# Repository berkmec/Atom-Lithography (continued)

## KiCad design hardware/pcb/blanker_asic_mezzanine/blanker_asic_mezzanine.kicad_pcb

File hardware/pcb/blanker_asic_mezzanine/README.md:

# Blanker ASIC Mezzanine PCB (`256-ch` `4×64` SKY130, `5 kV` Isolation, `53.3 V` HV Driver) & Live `ngspice-47` Verification

**BOM Coverage:** `S2.4-02`, `S2.4-01`, `S2.2-03`, `S2.4-03`, `S2.2-01`  
**Epistemic Status:** `M0/M1_DESIGN_ONLY` — `no_lab_measurement=true`, `no_physical_fab=true`, `iec61508_certified=false`, `semi_s2_certified=false`. Active semiconductors are `{Aday-COTS}` candidates; SKY130 tiles & LTCC/MEMS interfaces are `{Ozel-Uretim}`.

## 1. Modular `256-ch` (`4×` Boards = `1,024-ch`) Architecture (`blanker_asic_mezzanine.{kicad_sch,kicad_pcb}`)

Closes the `#281` Defect #6 cross-subsystem HV tension between the `-5,000 V ± 53.3 V` floating ion-column blanker deck (`DESIGN.md` / `S2.2-01`) and `1.8 V` SKY130 CMOS `blanker_tile.v` (`S2.4-01`):

- **Dimensions & Stackup:** `240 × 160 mm`, **`6` copper layers** (`SIG1-GND-SIG2-SIG3-PWR-SIG4`), `1.656 mm` total thickness, UHV low-outgassing **Rogers RO4350B (`ε_r = 3.48`) / Polyimide bondply (`ε_r = 3.40`)**.
- **Exact `src/rtl/blanker_tile.v` Interface (`4×` SKY130 `64-ch` Tiles = `256 ch` / board):**
  - All `13` RTL ports explicitly pinned and physically routed pad-to-pad across `U_TILE0..U_TILE3` (X-staggered `44-pin` ceramic QFP column) and `U_SERDES` (`54-pin` ceramic QFP): `clk`, `rst_n`, `cfg_we`, `cfg_addr[6:0]`, `cfg_data[7:0]`, `start_all`, `count_hit[63:0]`, `blanker_open[63:0]`, `busy_any`, `done_sticky`, `abort_sticky`, `rd_addr[5:0]`, `rd_counted[7:0]`.
- **`5 kV` Galvanic Isolation Barrier (`IEC 61010-1 / IPC-2221B`):**
  - Strictly partitioned primary Earth side (`x ≤ 34 mm`: `2× CF100` UHV flex harness connectors `S2.4-03`) vs. floating `-5 kV` deck (`x ≥ 58 mm`), separated by a `24 mm` copper-free moat across all 6 copper layers and a **`3.5 × 144.0 mm` milled `Edge.Cuts` air-slot**.
  - Wide-body `5 kVrms` reinforced bridging components (`THM15-2423WI-6KV` isolated DC-DC, `AFBR-1624Z/2624Z-5KV` optical control/data transceivers, dedicated `<25 ns` `ACPL-M61L-5KV` fast global override opto-isolator).
  - **Strict Geometric HV DRC:** Air clearance **`16.00 mm`** (`≥ 12.0 mm` req), slot-detour surface creepage **`25.70 mm`** (`≥ 15.0 mm` req), through-board dielectric stress PASS (`0` violations across all segments, vias, pads, and zones).
- **HV Push-Pull Deflector Array & LTCC Interposer (`S2.2-03`):**
  - `16× 16-ch` (`256 ch`) `1.8 V → 27–53.3 V` push-pull deflector level-shifter arrays (`U_HVDRV0..15`) with `50 Ω` damping resistors (`R_DAMP0..15`) fanning out to `J_LTCC_A/B` LTCC/AlN micro-bump ceramic interposer (`S2.2-03` → `S2.2-01` `0.50 mm` MEMS plate).
  - Hard-wired fail-safe global blank-override (`U_ISO_OVRD` → `U_OVRD_GATE` with `10 kΩ` fail-safe pull-down) forces ALL deflector plates to `V_deflect = +53.3 V` (HIGH = beam deflected to dump) on fault or loss of optical carrier.
- **Full Physical Connectivity, Controlled Impedance & Strict EDA Verification:** `63` components (`518` pads), `124` nets, **`routed = 124 / 124` (`100%`)**, **`unconnected_items = 0`**, **`track_dangling_count = 0`**, **`2,250` copper segments**, **`525` vias**, `4` partitioned copper zones, `1` milled air-slot, **`0` ERC errors**, **`0` DRC errors**, **`98 / 98`** `50 Ω SE` / `100 Ω diff` impedance checks PASS (`max error 0.005% ≤ 5.0%`), `min_measured_clearance = 0.1462 mm ≥ 0.127 mm`.

## 2. Live `ngspice-47` HV Switching & Global Override Verification (`blanker_hv_driver.cir`)

Transistor-level native `ngspice-47 -b` simulation (exit `0`, `0` errors, `0` warnings) of the `1.8 V` CMOS override NAND → `5 V` pre-driver → **zero-static-power pulsed-edge high-side CMOS latch** `53.3 V` push-pull stage driving realistic MEMS plate load (`C_plate = 5 pF` + `C_int = 2 pF` + `L_trace = 5 nH` + `R_damp = 50 Ω`), including a `25 ns` `5 kV` opto-isolator propagation delay on the override path:

| Metric | `ngspice-47` Measured | Target / Spec | Status |
| :--- | :---: | :---: | :---: |
| Steady-State Deflector Levels (`V_hi` / `V_lo` / `V_ovrd`) | `53.30 V` / `0.000 V` / `53.30 V` | `53.3 V` / `0 V` / `53.3 V` | **PASS** |
| `10–90%` Rise Time (`0 → 53.3 V`, `7 pF` MEMS load) | **`2.096 ns`** | `< 100 ns` | **PASS** |
| `90–10%` Fall Time (`53.3 → 0 V`, `7 pF` MEMS load) | **`2.223 ns`** | `< 100 ns` | **PASS** |
| End-to-End Global Blank-Override Clamp (incl. `5 kV` opto delay, while `blanker_open` stuck HIGH) | **`51.344 ns`** | `< 200 ns` (`<< 1 µs`) | **PASS** |
| HV Rail Static Dissipation (pulsed-edge latch) | `28.4 µW/ch` (`7.3 mW` / 256 ch) | Minimal UHV heat load | **PASS** |
| Switching Energy / Cycle (`E_hv` vs `C_tot·V² = 19.89 nJ`) | `77.47 nJ/cycle` (incl. HV gate/latch charge) | Bounded | **PASS** |
| `256-ch` Board Total Power (`1 kHz` nominal / `50 kHz` burst) | **`27.34 mW`** / **`1.009 W`** (`1,024-ch @ 1 kHz = 109.3 mW`) | `< 5 W` isolated DC-DC | **PASS** |

## 3. Reproducibility

```bash
PYTHONPATH=.:src python -B hardware/pcb/blanker_asic_mezzanine/build_blanker_mezzanine.py
PYTHONPATH=.:src pytest tests/test_pcb_fpga_blanker_cryo.py -v -p no:cacheprovider
```

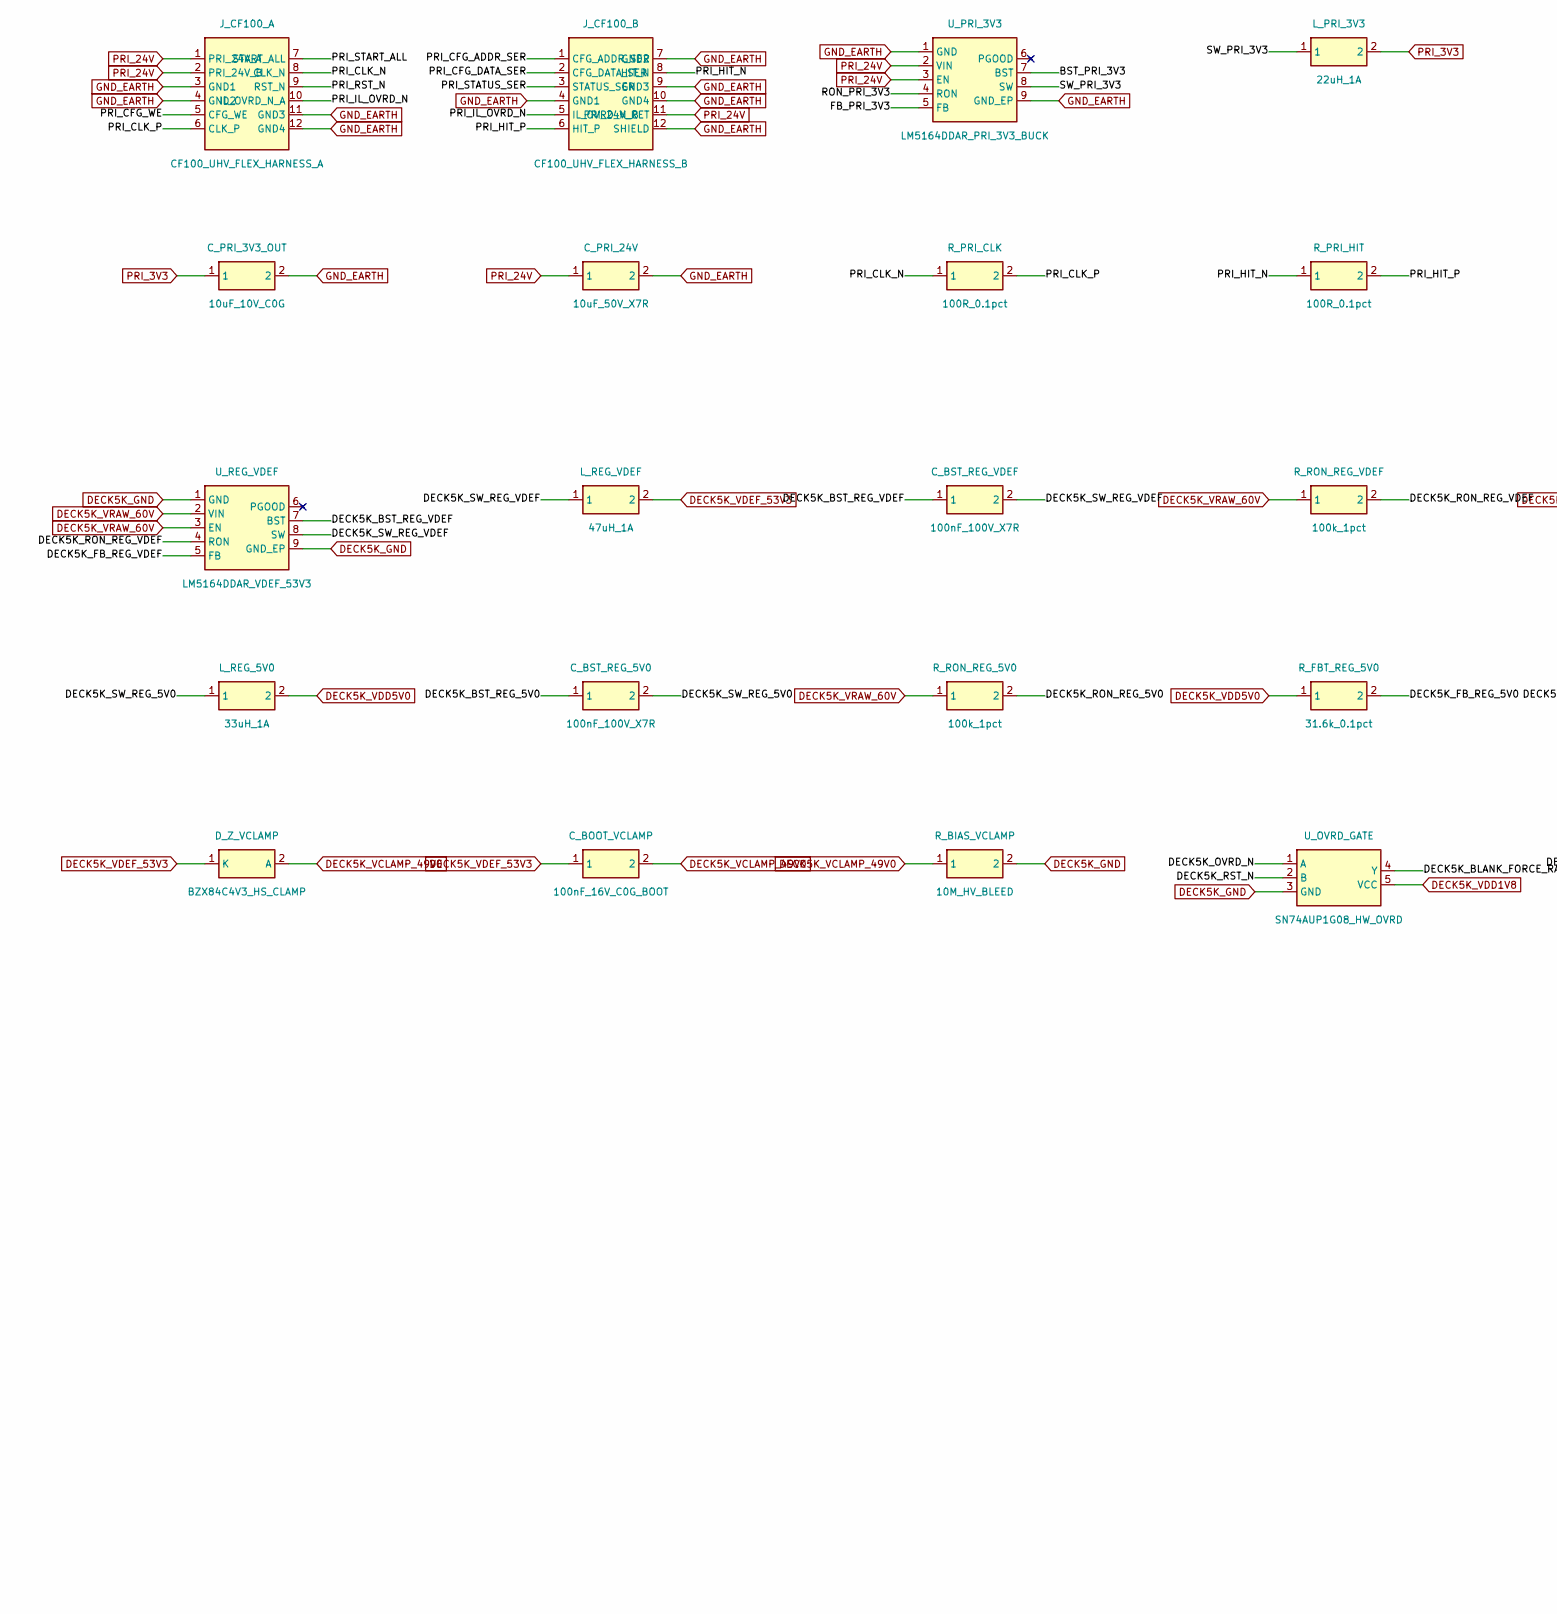
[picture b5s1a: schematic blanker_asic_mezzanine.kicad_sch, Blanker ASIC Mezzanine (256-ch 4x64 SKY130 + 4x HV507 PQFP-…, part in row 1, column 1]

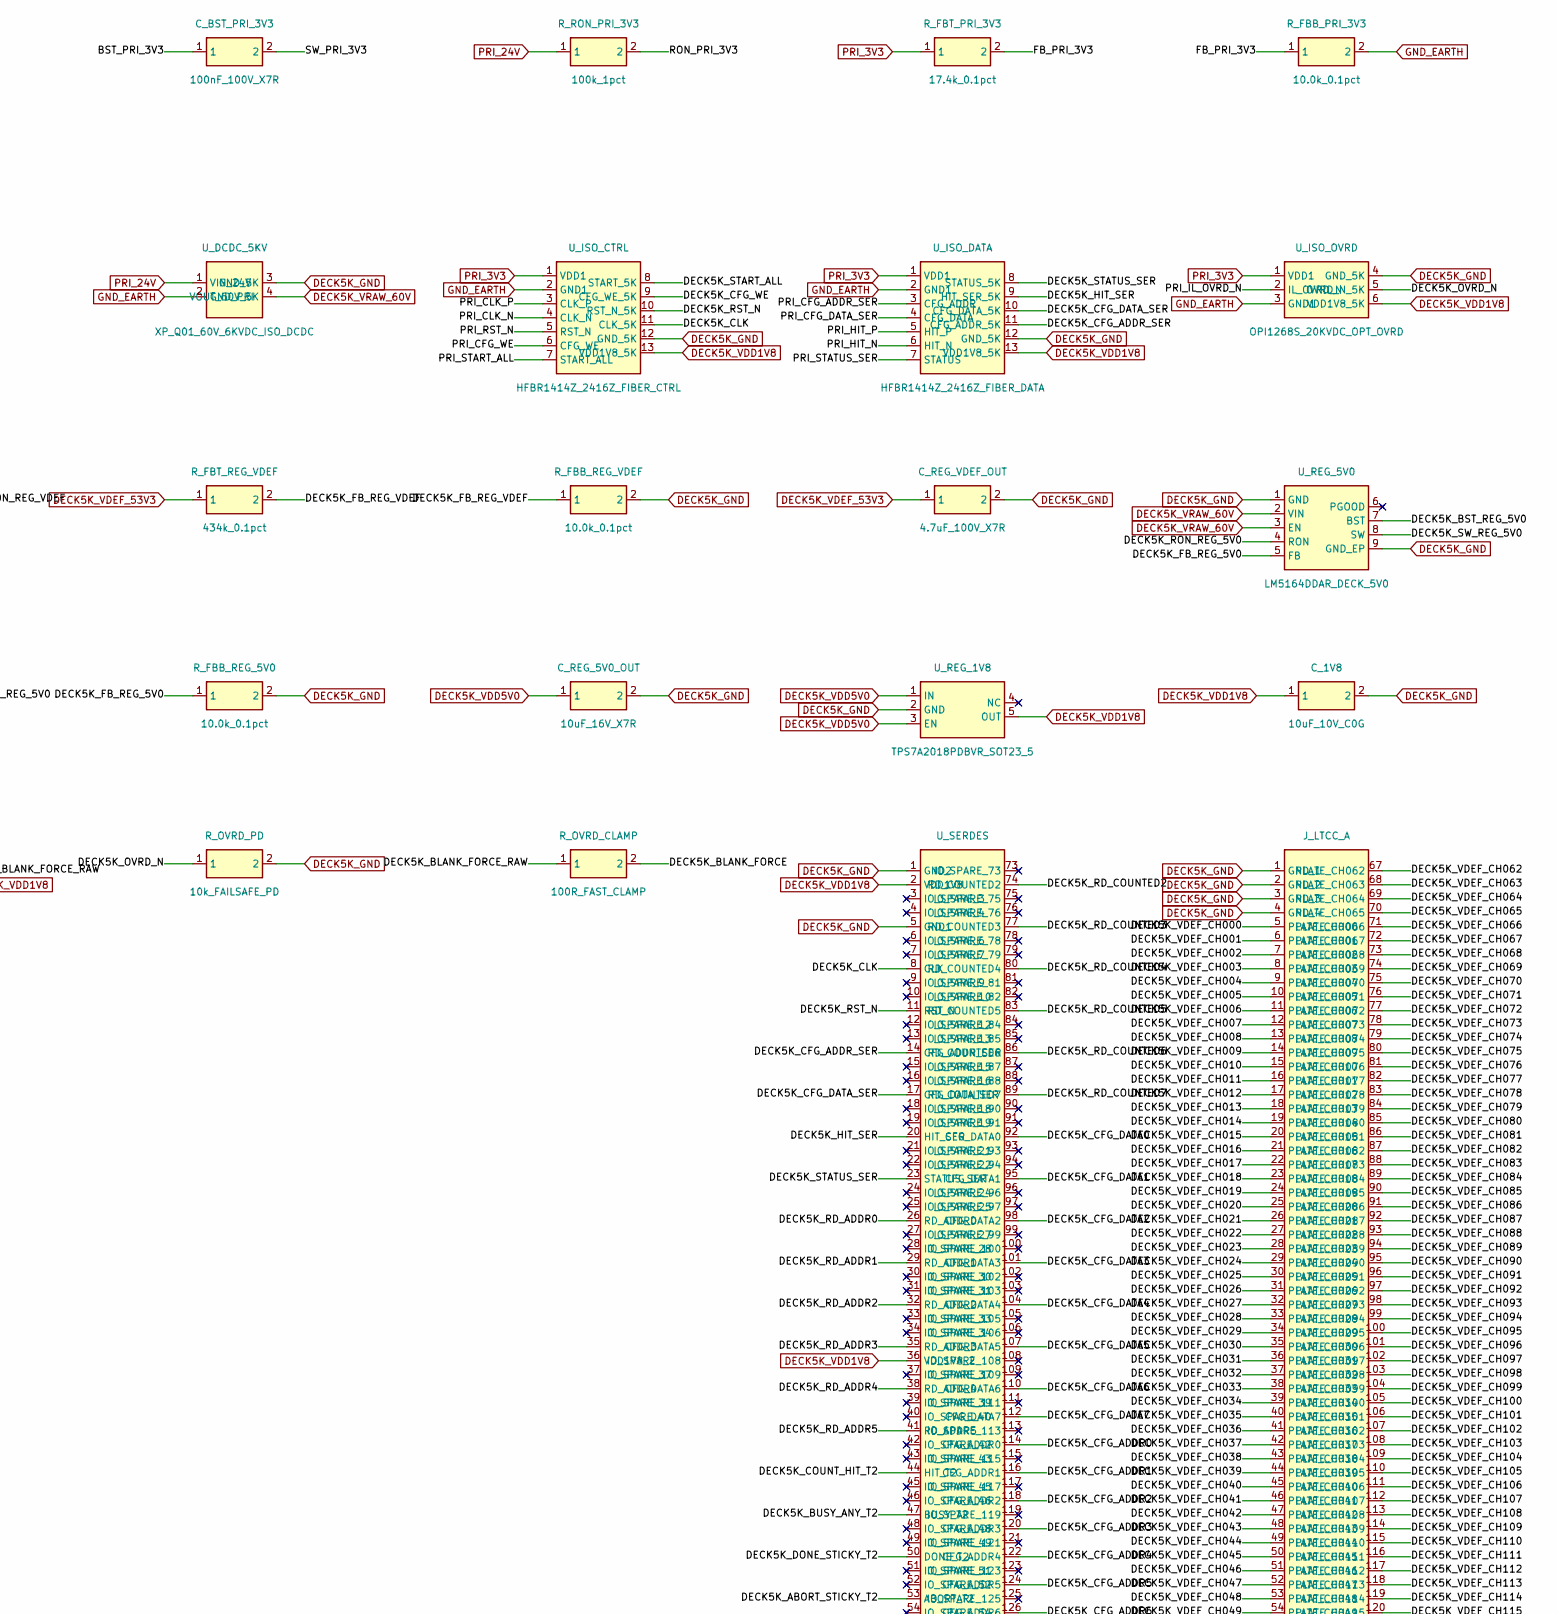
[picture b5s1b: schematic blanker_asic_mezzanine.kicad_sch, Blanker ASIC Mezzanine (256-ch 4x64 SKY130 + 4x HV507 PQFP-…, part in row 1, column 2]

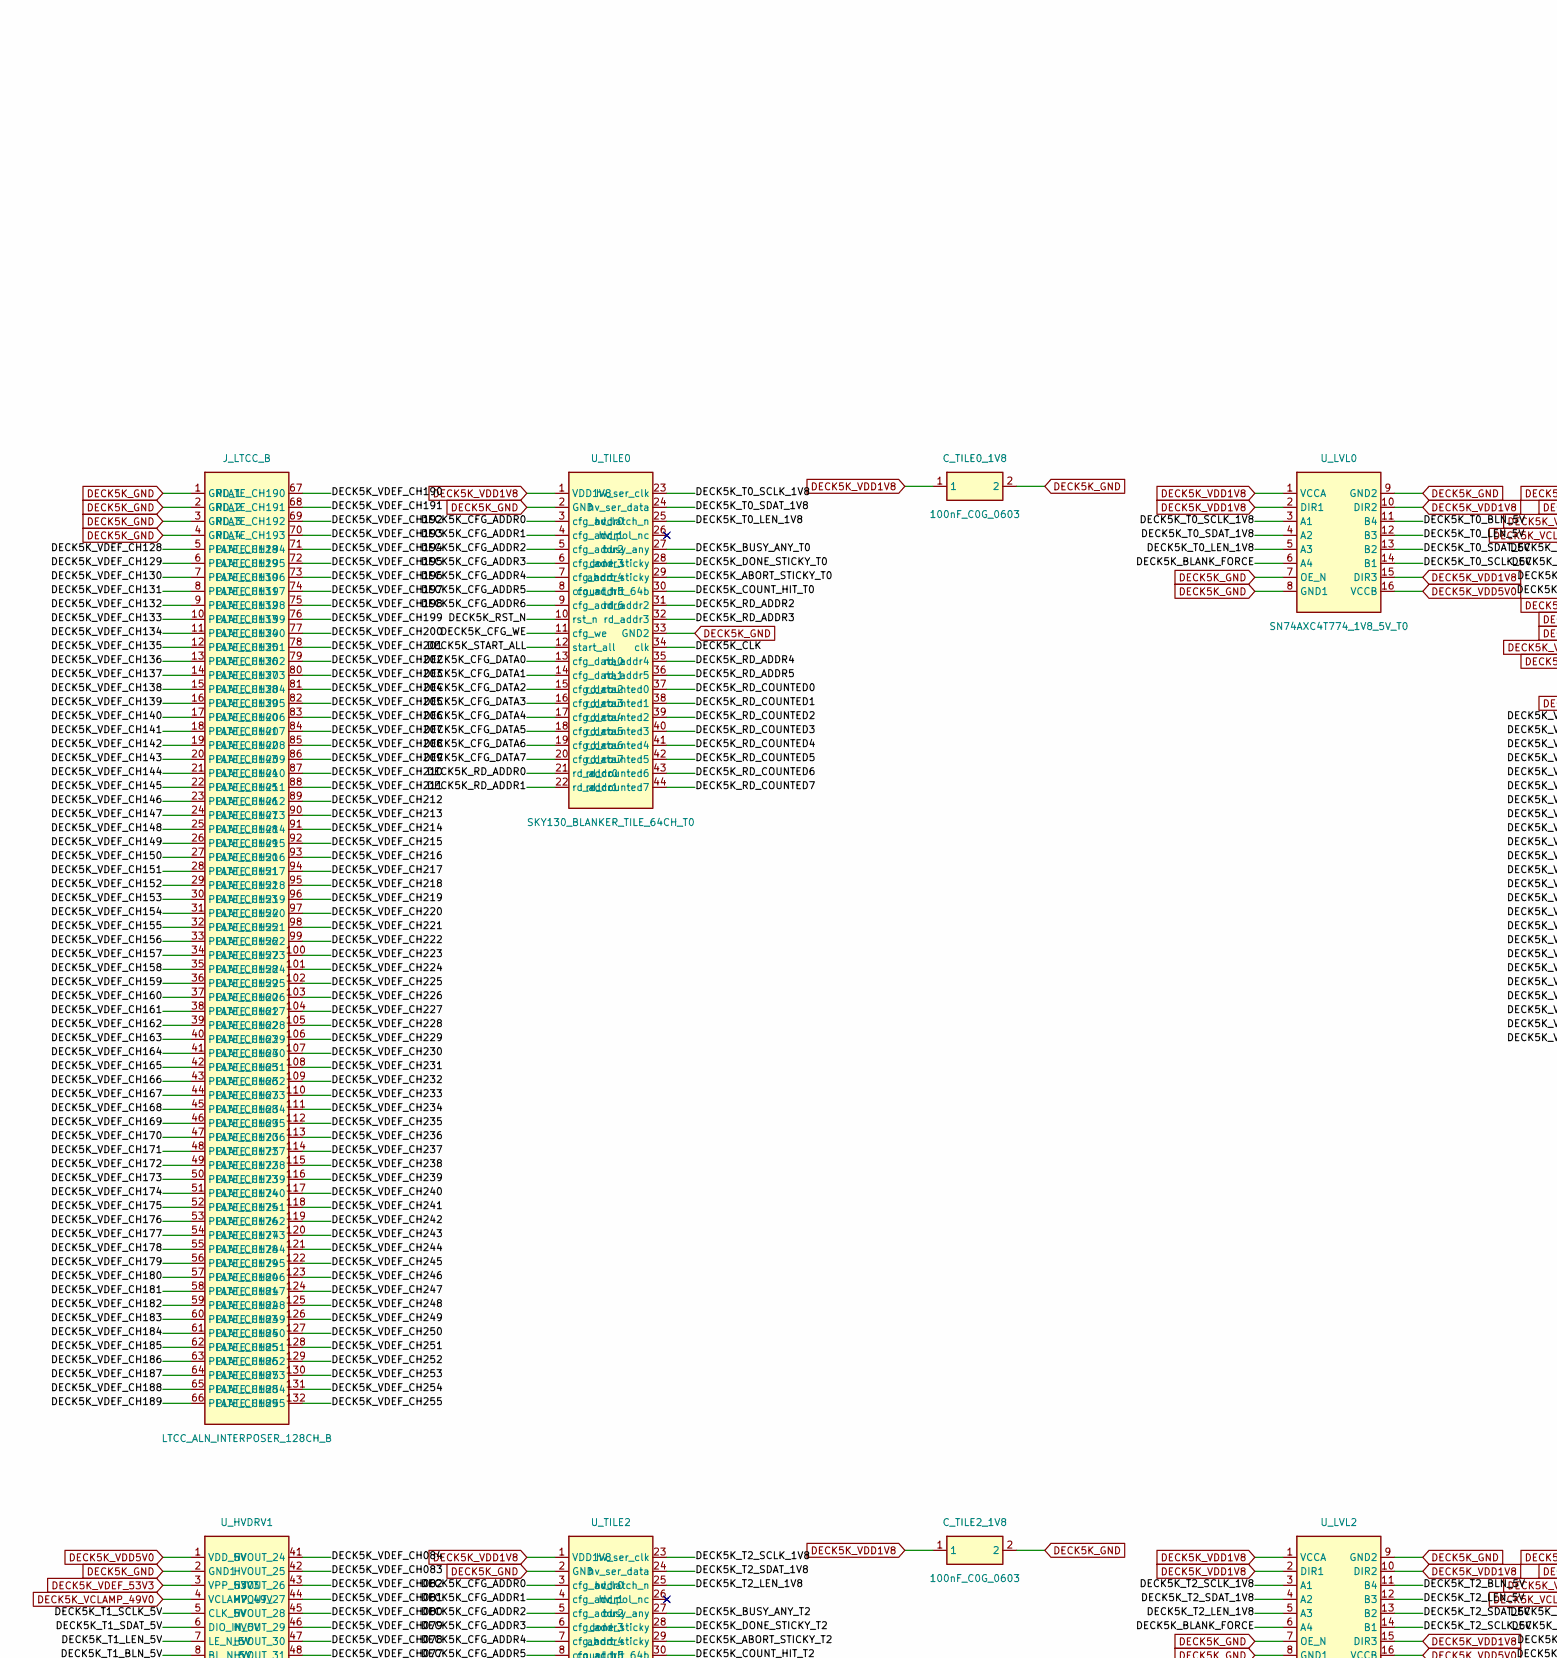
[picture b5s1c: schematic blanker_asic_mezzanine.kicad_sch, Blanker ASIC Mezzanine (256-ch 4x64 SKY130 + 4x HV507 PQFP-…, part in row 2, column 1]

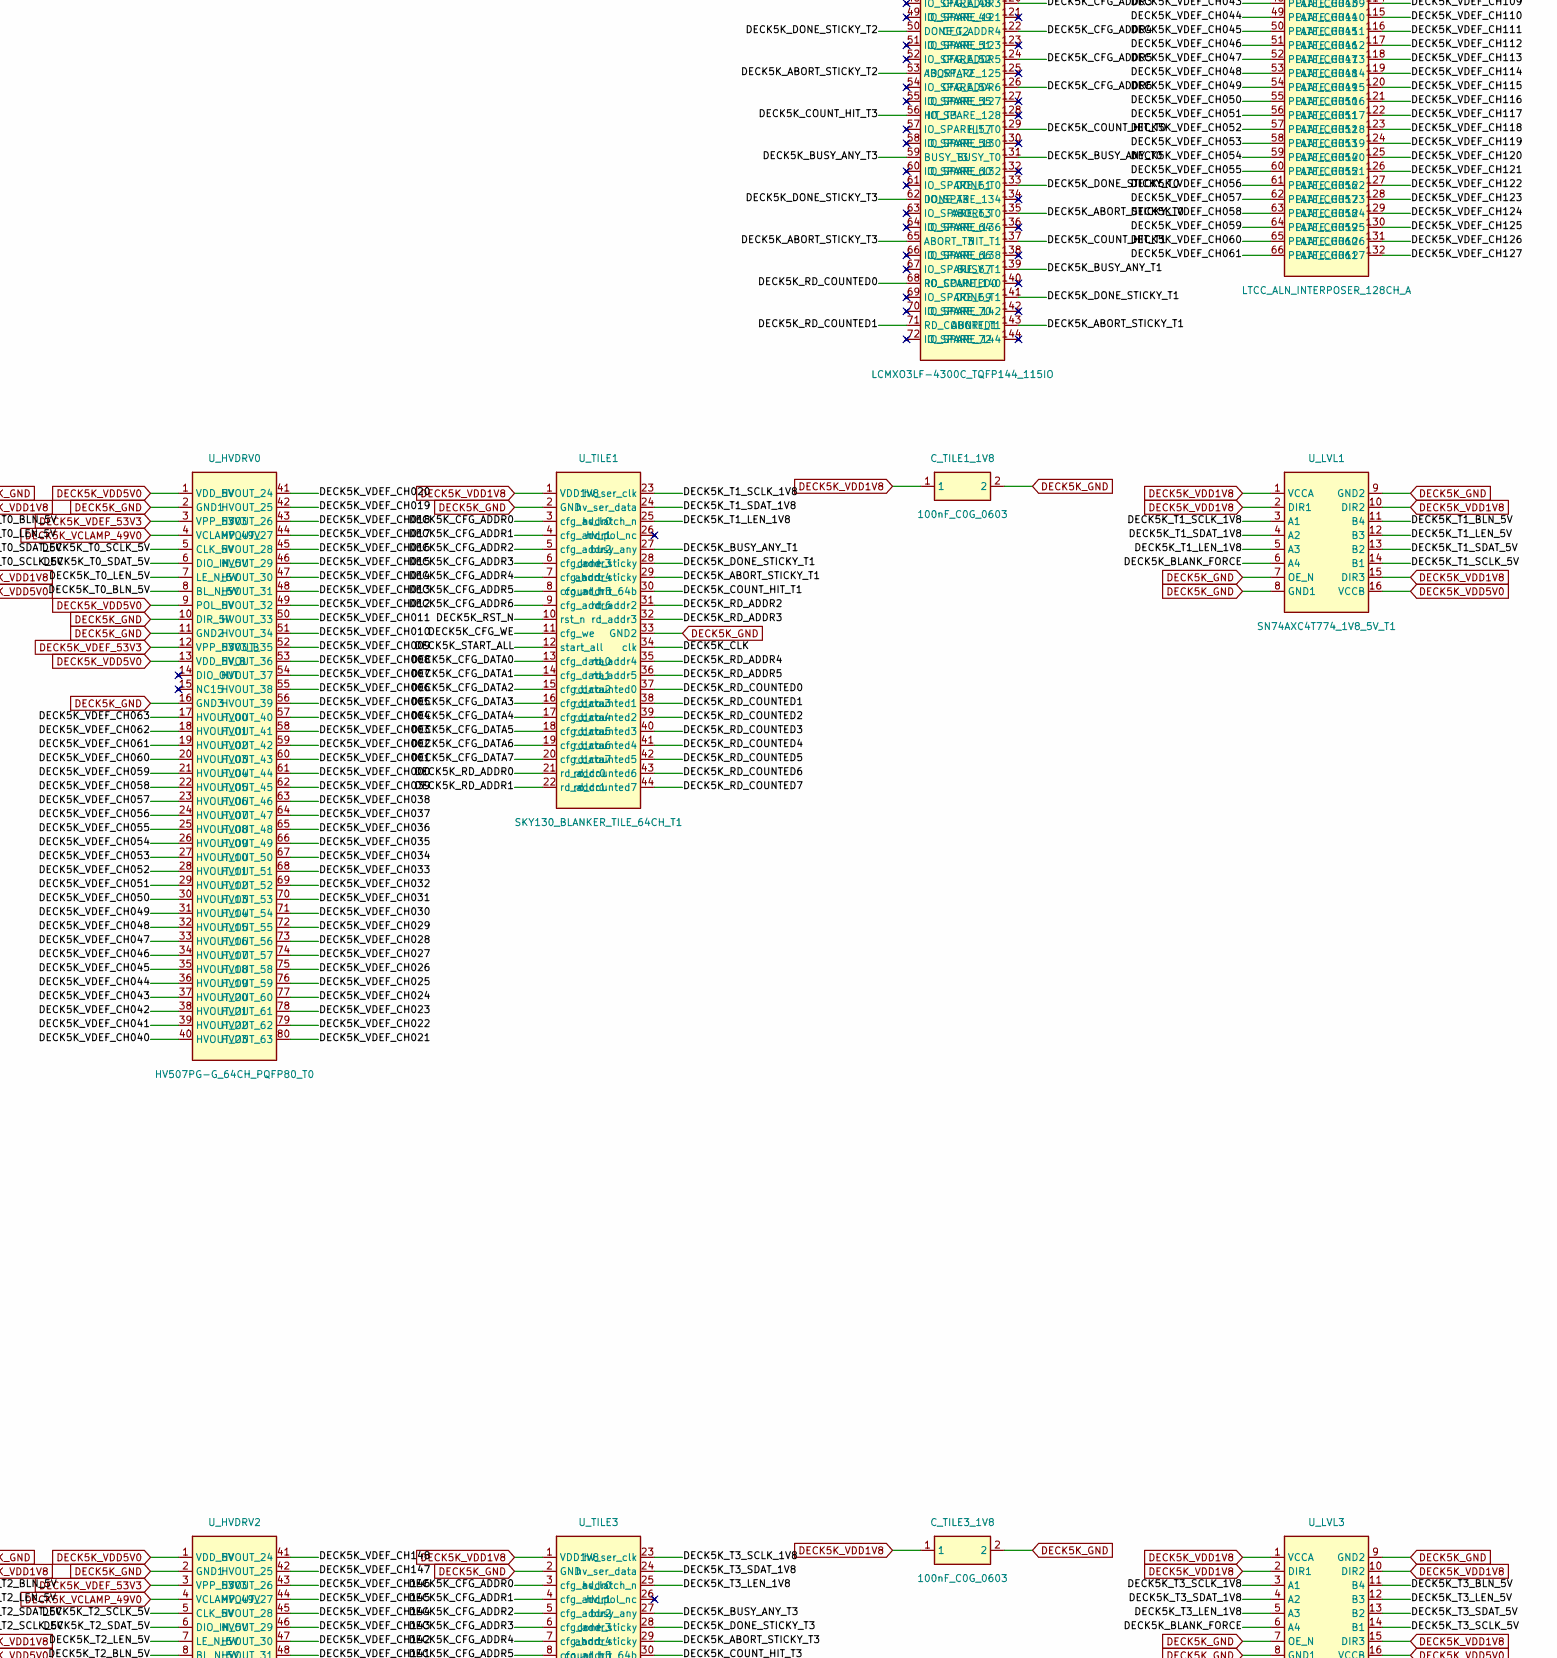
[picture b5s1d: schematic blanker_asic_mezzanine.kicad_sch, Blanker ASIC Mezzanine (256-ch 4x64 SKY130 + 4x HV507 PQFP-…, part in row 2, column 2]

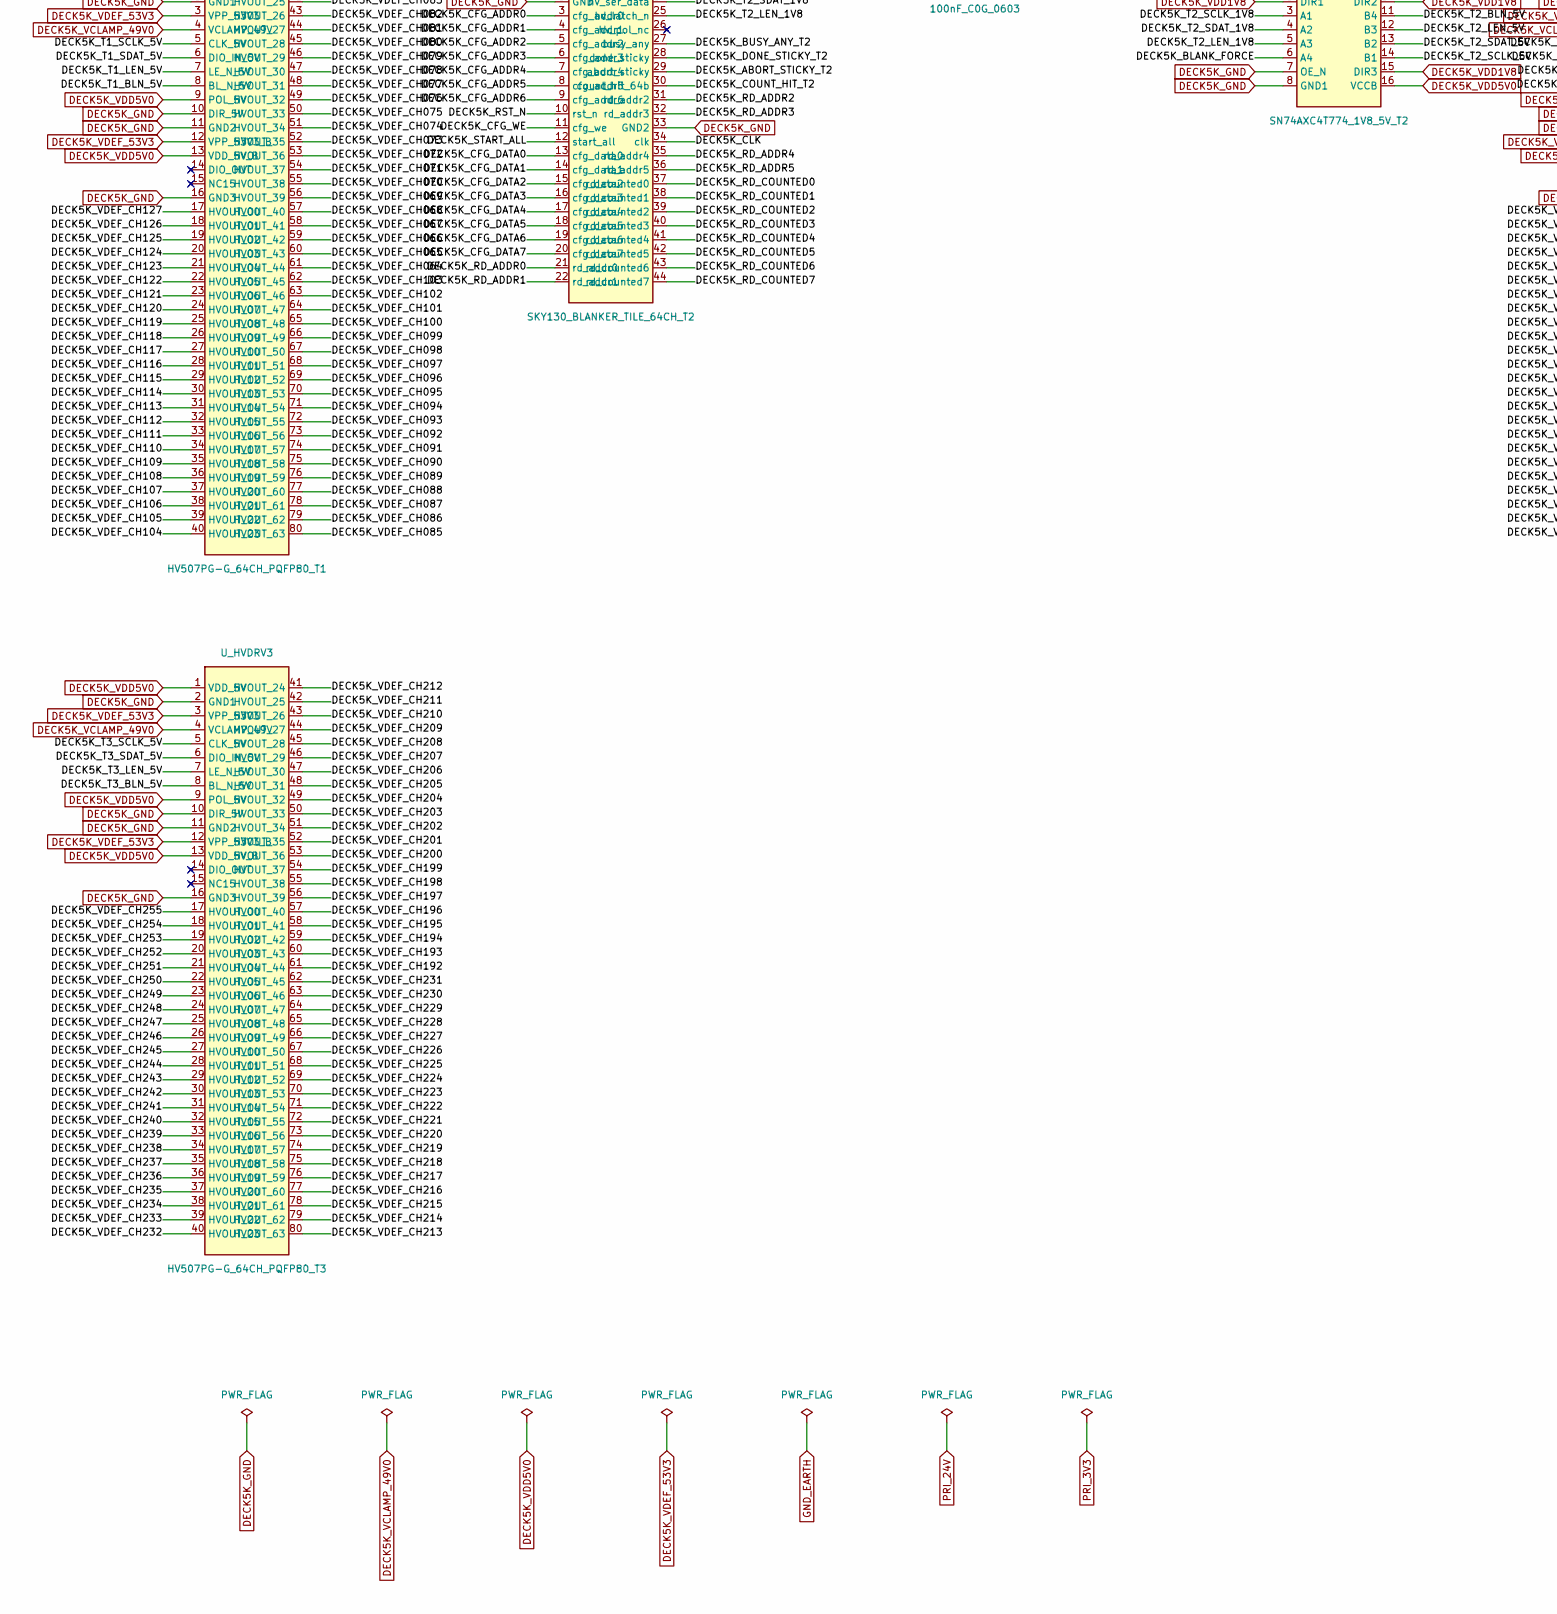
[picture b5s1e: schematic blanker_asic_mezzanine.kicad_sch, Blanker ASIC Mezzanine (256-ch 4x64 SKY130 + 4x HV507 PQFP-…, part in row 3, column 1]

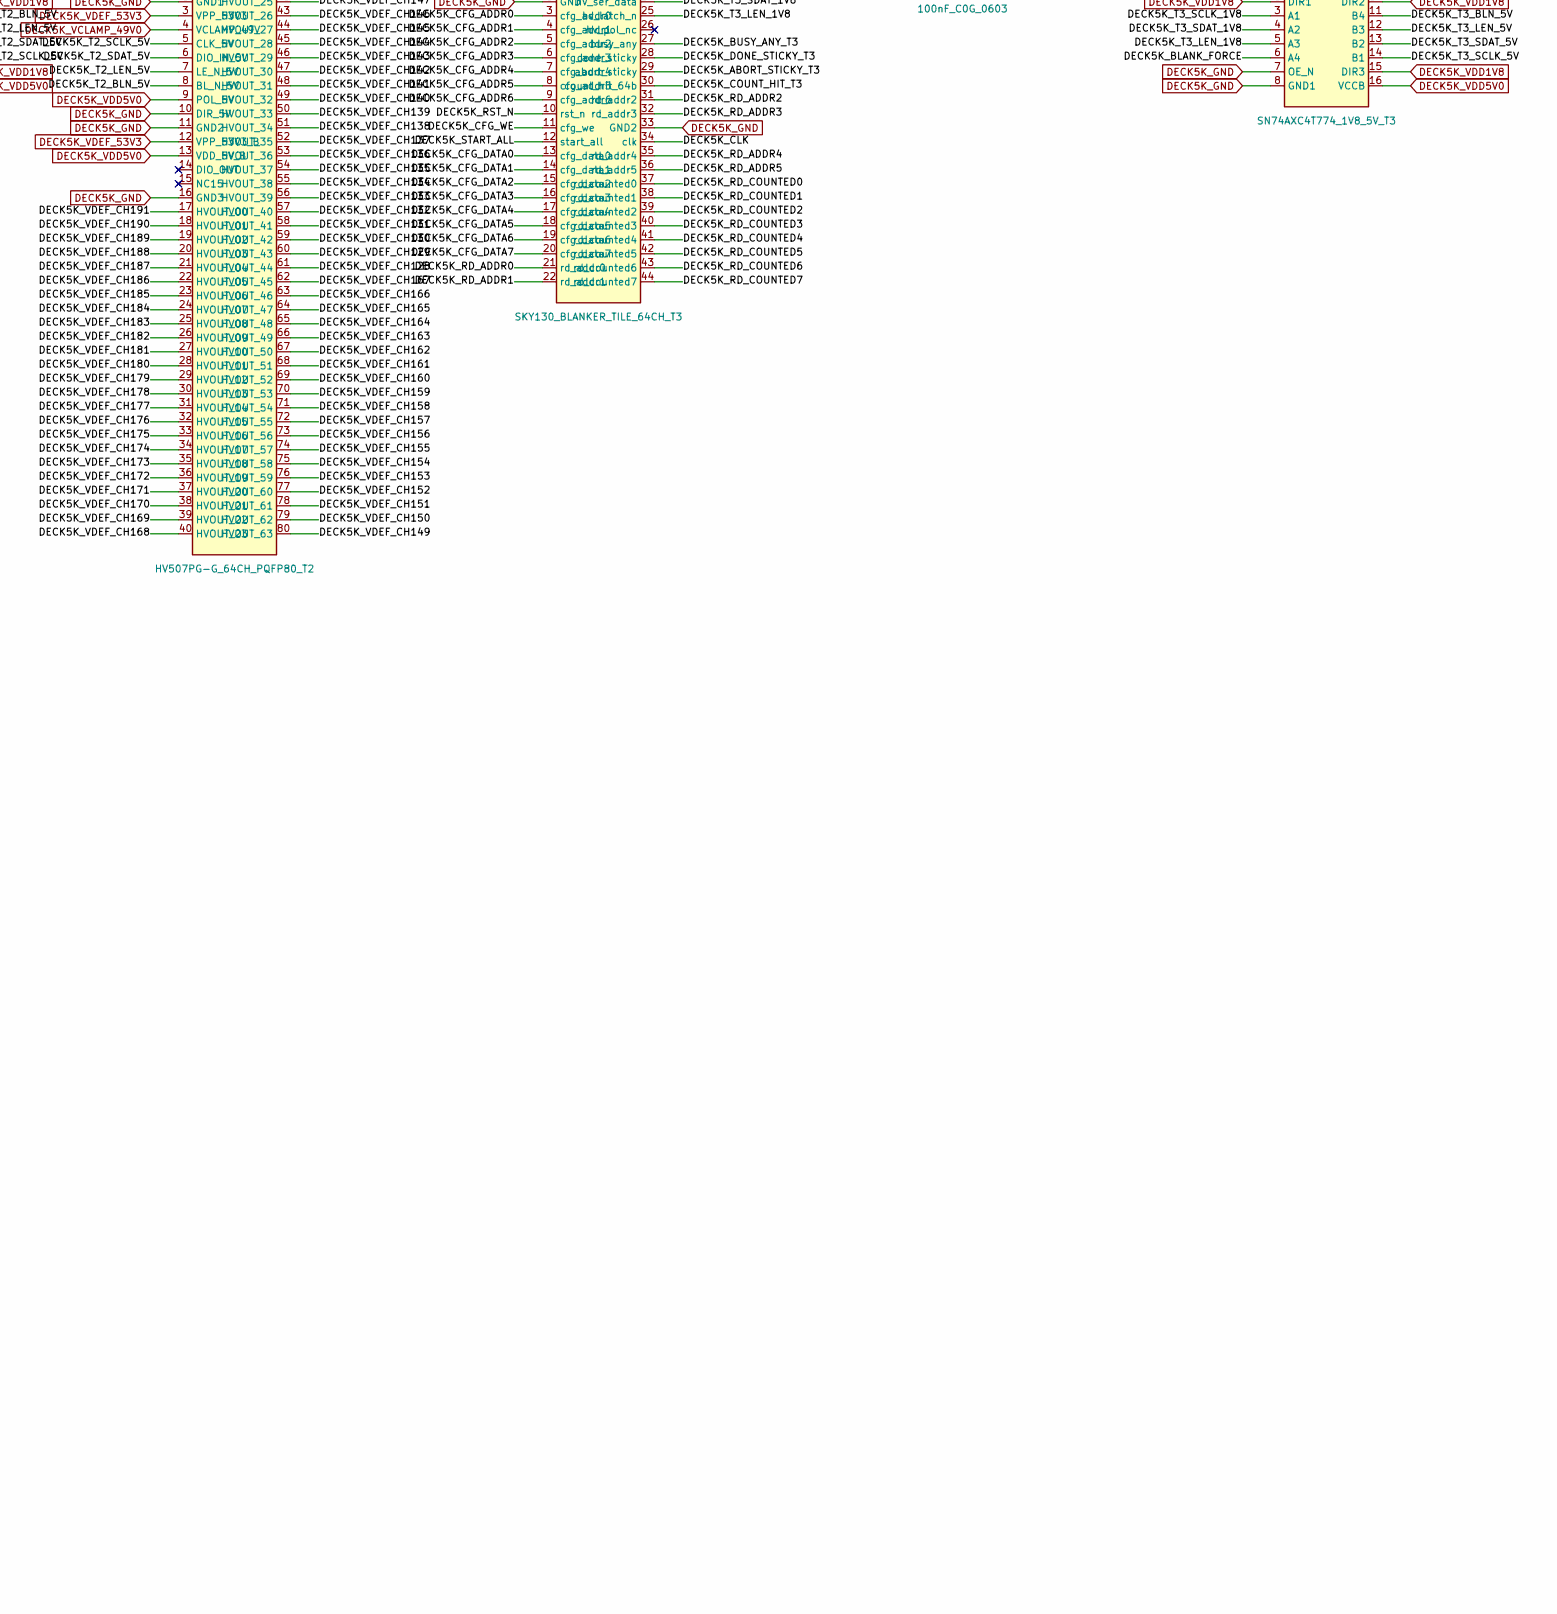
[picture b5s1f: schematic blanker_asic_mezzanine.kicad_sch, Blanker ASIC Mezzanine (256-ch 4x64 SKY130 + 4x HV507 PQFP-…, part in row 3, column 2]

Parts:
C_1V8: 10uF_10V_C0G; C_0805_2012Metric; MPN 10uF_10V_C0G
C_BOOT_VCLAMP: 100nF_16V_C0G_BOOT; C_0805_2012Metric; MPN 100nF_16V_C0G_BOOT
C_BST_PRI_3V3: 100nF_100V_X7R; C_0603_1608Metric; MPN 100nF_100V_X7R
C_BST_REG_5V0: 100nF_100V_X7R; C_0603_1608Metric; MPN 100nF_100V_X7R
C_BST_REG_VDEF: 100nF_100V_X7R; C_0603_1608Metric; MPN 100nF_100V_X7R
C_PRI_3V3_OUT: 10uF_10V_C0G; C_1206_3216Metric; MPN 10uF_10V_C0G
C_PRI_24V: 10uF_50V_X7R; C_1206_3216Metric; MPN 10uF_50V_X7R
C_REG_5V0_OUT: 10uF_16V_X7R; C_1206_3216Metric; MPN 10uF_16V_X7R
C_REG_VDEF_OUT: 4.7uF_100V_X7R; C_1206_3216Metric; MPN 4.7uF_100V_X7R
C_TILE0_1V8, C_TILE1_1V8, C_TILE2_1V8, C_TILE3_1V8: 100nF_C0G_0603; C_0603_1608Metric; MPN 100nF_C0G_0603
D_Z_VCLAMP: BZX84C4V3_HS_CLAMP; D_0805_2012Metric; MPN BZX84C4V3_HS_CLAMP
J_CF100_A: CF100_UHV_FLEX_HARNESS_A; HDR_2x6_2.54mm; MPN CF100_UHV_FLEX_HARNESS_A
J_CF100_B: CF100_UHV_FLEX_HARNESS_B; HDR_2x6_2.54mm; MPN CF100_UHV_FLEX_HARNESS_B
J_LTCC_A: LTCC_ALN_INTERPOSER_128CH_A; LTCC_MICROBUMP_132P; MPN LTCC_ALN_INTERPOSER_128CH_A
J_LTCC_B: LTCC_ALN_INTERPOSER_128CH_B; LTCC_MICROBUMP_132P; MPN LTCC_ALN_INTERPOSER_128CH_B
L_PRI_3V3: 22uH_1A; L_1210_3225Metric; MPN 22uH_1A
L_REG_5V0: 33uH_1A; L_1210_3225Metric; MPN 33uH_1A
L_REG_VDEF: 47uH_1A; L_1210_3225Metric; MPN 47uH_1A
R_BIAS_VCLAMP: 10M_HV_BLEED; R_0805_2012Metric; MPN 10M_HV_BLEED
R_FBB_PRI_3V3: 10.0k_0.1pct; R_0603_1608Metric; MPN 10.0k_0.1pct
R_FBB_REG_5V0: 10.0k_0.1pct; R_0603_1608Metric; MPN 10.0k_0.1pct
R_FBB_REG_VDEF: 10.0k_0.1pct; R_0603_1608Metric; MPN 10.0k_0.1pct
R_FBT_PRI_3V3: 17.4k_0.1pct; R_0603_1608Metric; MPN 17.4k_0.1pct
R_FBT_REG_5V0: 31.6k_0.1pct; R_0603_1608Metric; MPN 31.6k_0.1pct
R_FBT_REG_VDEF: 434k_0.1pct; R_0603_1608Metric; MPN 434k_0.1pct
R_OVRD_CLAMP: 100R_FAST_CLAMP; R_0603_1608Metric; MPN 100R_FAST_CLAMP
R_OVRD_PD: 10k_FAILSAFE_PD; R_0603_1608Metric; MPN 10k_FAILSAFE_PD
R_PRI_CLK: 100R_0.1pct; R_0603_1608Metric; MPN 100R_0.1pct
R_PRI_HIT: 100R_0.1pct; R_0603_1608Metric; MPN 100R_0.1pct
R_RON_PRI_3V3: 100k_1pct; R_0603_1608Metric; MPN 100k_1pct
R_RON_REG_5V0: 100k_1pct; R_0603_1608Metric; MPN 100k_1pct
R_RON_REG_VDEF: 100k_1pct; R_0603_1608Metric; MPN 100k_1pct
U_DCDC_5KV: XP_Q01_60V_6KVDC_ISO_DCDC; ISO_6KVDC_60V_P28mm; MPN XP_Power_Q01-60V-6KV
U_HVDRV0: HV507PG-G_64CH_PQFP80_T0; PQFP-80_14x20mm_P0.8mm; MPN Microchip_HV507PG-G
U_HVDRV1: HV507PG-G_64CH_PQFP80_T1; PQFP-80_14x20mm_P0.8mm; MPN Microchip_HV507PG-G
U_HVDRV2: HV507PG-G_64CH_PQFP80_T2; PQFP-80_14x20mm_P0.8mm; MPN Microchip_HV507PG-G
U_HVDRV3: HV507PG-G_64CH_PQFP80_T3; PQFP-80_14x20mm_P0.8mm; MPN Microchip_HV507PG-G
U_ISO_CTRL: HFBR1414Z_2416Z_FIBER_CTRL; FIBER_TXRX_6KV_P28mm; MPN Broadcom_HFBR-1414Z_2416Z
U_ISO_DATA: HFBR1414Z_2416Z_FIBER_DATA; FIBER_TXRX_6KV_P28mm; MPN Broadcom_HFBR-1414Z_2416Z
U_ISO_OVRD: OPI1268S_20KVDC_OPT_OVRD; OPI1268S_20KV_P28mm; MPN Vishay_OPI1268S-20KV
U_LVL0: SN74AXC4T774_1V8_5V_T0; TSSOP-16_4.4x5mm_P0.65mm; MPN SN74AXC4T774PWR
U_LVL1: SN74AXC4T774_1V8_5V_T1; TSSOP-16_4.4x5mm_P0.65mm; MPN SN74AXC4T774PWR
U_LVL2: SN74AXC4T774_1V8_5V_T2; TSSOP-16_4.4x5mm_P0.65mm; MPN SN74AXC4T774PWR
U_LVL3: SN74AXC4T774_1V8_5V_T3; TSSOP-16_4.4x5mm_P0.65mm; MPN SN74AXC4T774PWR
U_OVRD_GATE: SN74AUP1G08_HW_OVRD; SOT-23-5; MPN SN74AUP1G08DCKR
U_PRI_3V3: LM5164DDAR_PRI_3V3_BUCK; SOIC-8-1EP_3.9x4.9mm_P1.27mm_EP2.29x3mm; MPN LM5164DDAR
U_REG_1V8: TPS7A2018PDBVR_SOT23_5; SOT-23-5; MPN TPS7A2018PDBVR
U_REG_5V0: LM5164DDAR_DECK_5V0; SOIC-8-1EP_3.9x4.9mm_P1.27mm_EP2.29x3mm; MPN LM5164DDAR
U_REG_VDEF: LM5164DDAR_VDEF_53V3; SOIC-8-1EP_3.9x4.9mm_P1.27mm_EP2.29x3mm; MPN LM5164DDAR
U_SERDES: LCMXO3LF-4300C_TQFP144_115IO; TQFP-144_20x20mm_P0.5mm; MPN LCMXO3LF-4300C-5TG144I
U_TILE0: SKY130_BLANKER_TILE_64CH_T0; SKY130_CERAMIC_QFP44_20x20mm_P1.5mm; MPN SKY130-BLANKER-TILE-64CH
U_TILE1: SKY130_BLANKER_TILE_64CH_T1; SKY130_CERAMIC_QFP44_20x20mm_P1.5mm; MPN SKY130-BLANKER-TILE-64CH
U_TILE2: SKY130_BLANKER_TILE_64CH_T2; SKY130_CERAMIC_QFP44_20x20mm_P1.5mm; MPN SKY130-BLANKER-TILE-64CH
U_TILE3: SKY130_BLANKER_TILE_64CH_T3; SKY130_CERAMIC_QFP44_20x20mm_P1.5mm; MPN SKY130-BLANKER-TILE-64CH

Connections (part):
BST_PRI_3V3: C_BST_PRI_3V3.1, U_PRI_3V3.7 (BST)
DECK5K_ABORT_STICKY_T0: U_SERDES.135 (ABORT_T0), U_TILE0.29 (abort_sticky)
DECK5K_ABORT_STICKY_T1: U_SERDES.143 (ABORT_T1), U_TILE1.29 (abort_sticky)
DECK5K_ABORT_STICKY_T2: U_SERDES.53 (ABORT_T2), U_TILE2.29 (abort_sticky)
DECK5K_ABORT_STICKY_T3: U_SERDES.65 (ABORT_T3), U_TILE3.29 (abort_sticky)
DECK5K_BLANK_FORCE: R_OVRD_CLAMP.2, U_LVL0.6 (A4), U_LVL1.6 (A4), U_LVL2.6 (A4), U_LVL3.6 (A4)
DECK5K_BLANK_FORCE_RAW: R_OVRD_CLAMP.1, U_OVRD_GATE.4 (Y)
DECK5K_BST_REG_5V0: C_BST_REG_5V0.1, U_REG_5V0.7 (BST)
DECK5K_BST_REG_VDEF: C_BST_REG_VDEF.1, U_REG_VDEF.7 (BST)
DECK5K_BUSY_ANY_T0: U_SERDES.131 (BUSY_T0), U_TILE0.27 (busy_any)
DECK5K_BUSY_ANY_T1: U_SERDES.139 (BUSY_T1), U_TILE1.27 (busy_any)
DECK5K_BUSY_ANY_T2: U_SERDES.47 (BUSY_T2), U_TILE2.27 (busy_any)
DECK5K_BUSY_ANY_T3: U_SERDES.59 (BUSY_T3), U_TILE3.27 (busy_any)
DECK5K_CFG_ADDR0: U_SERDES.114 (CFG_ADDR0), U_TILE0.3 (cfg_addr0), U_TILE1.3 (cfg_addr0), U_TILE2.3 (cfg_addr0), U_TILE3.3 (cfg_addr0)
DECK5K_CFG_ADDR1: U_SERDES.116 (CFG_ADDR1), U_TILE0.4 (cfg_addr1), U_TILE1.4 (cfg_addr1), U_TILE2.4 (cfg_addr1), U_TILE3.4 (cfg_addr1)
DECK5K_CFG_ADDR2: U_SERDES.118 (CFG_ADDR2), U_TILE0.5 (cfg_addr2), U_TILE1.5 (cfg_addr2), U_TILE2.5 (cfg_addr2), U_TILE3.5 (cfg_addr2)
DECK5K_CFG_ADDR3: U_SERDES.120 (CFG_ADDR3), U_TILE0.6 (cfg_addr3), U_TILE1.6 (cfg_addr3), U_TILE2.6 (cfg_addr3), U_TILE3.6 (cfg_addr3)
DECK5K_CFG_ADDR4: U_SERDES.122 (CFG_ADDR4), U_TILE0.7 (cfg_addr4), U_TILE1.7 (cfg_addr4), U_TILE2.7 (cfg_addr4), U_TILE3.7 (cfg_addr4)
DECK5K_CFG_ADDR5: U_SERDES.124 (CFG_ADDR5), U_TILE0.8 (cfg_addr5), U_TILE1.8 (cfg_addr5), U_TILE2.8 (cfg_addr5), U_TILE3.8 (cfg_addr5)
DECK5K_CFG_ADDR6: U_SERDES.126 (CFG_ADDR6), U_TILE0.9 (cfg_addr6), U_TILE1.9 (cfg_addr6), U_TILE2.9 (cfg_addr6), U_TILE3.9 (cfg_addr6)
DECK5K_CFG_ADDR_SER: U_ISO_DATA.11 (CFG_ADDR_5K), U_SERDES.14 (CFG_ADDR_SER)
DECK5K_CFG_DATA0: U_SERDES.92 (CFG_DATA0), U_TILE0.13 (cfg_data0), U_TILE1.13 (cfg_data0), U_TILE2.13 (cfg_data0), U_TILE3.13 (cfg_data0)
DECK5K_CFG_DATA1: U_SERDES.95 (CFG_DATA1), U_TILE0.14 (cfg_data1), U_TILE1.14 (cfg_data1), U_TILE2.14 (cfg_data1), U_TILE3.14 (cfg_data1)
DECK5K_CFG_DATA2: U_SERDES.98 (CFG_DATA2), U_TILE0.15 (cfg_data2), U_TILE1.15 (cfg_data2), U_TILE2.15 (cfg_data2), U_TILE3.15 (cfg_data2)
DECK5K_CFG_DATA3: U_SERDES.101 (CFG_DATA3), U_TILE0.16 (cfg_data3), U_TILE1.16 (cfg_data3), U_TILE2.16 (cfg_data3), U_TILE3.16 (cfg_data3)
DECK5K_CFG_DATA4: U_SERDES.104 (CFG_DATA4), U_TILE0.17 (cfg_data4), U_TILE1.17 (cfg_data4), U_TILE2.17 (cfg_data4), U_TILE3.17 (cfg_data4)
DECK5K_CFG_DATA5: U_SERDES.107 (CFG_DATA5), U_TILE0.18 (cfg_data5), U_TILE1.18 (cfg_data5), U_TILE2.18 (cfg_data5), U_TILE3.18 (cfg_data5)
DECK5K_CFG_DATA6: U_SERDES.110 (CFG_DATA6), U_TILE0.19 (cfg_data6), U_TILE1.19 (cfg_data6), U_TILE2.19 (cfg_data6), U_TILE3.19 (cfg_data6)
DECK5K_CFG_DATA7: U_SERDES.112 (CFG_DATA7), U_TILE0.20 (cfg_data7), U_TILE1.20 (cfg_data7), U_TILE2.20 (cfg_data7), U_TILE3.20 (cfg_data7)
DECK5K_CFG_DATA_SER: U_ISO_DATA.10 (CFG_DATA_5K), U_SERDES.17 (CFG_DATA_SER)
DECK5K_CFG_WE: U_ISO_CTRL.9 (CFG_WE_5K), U_TILE0.11 (cfg_we), U_TILE1.11 (cfg_we), U_TILE2.11 (cfg_we), U_TILE3.11 (cfg_we)
DECK5K_CLK: U_ISO_CTRL.11 (CLK_5K), U_SERDES.8 (CLK), U_TILE0.34 (clk), U_TILE1.34 (clk), U_TILE2.34 (clk), U_TILE3.34 (clk)
DECK5K_COUNT_HIT_T0: U_SERDES.129 (HIT_T0), U_TILE0.30 (count_hit_64b)
DECK5K_COUNT_HIT_T1: U_SERDES.137 (HIT_T1), U_TILE1.30 (count_hit_64b)
DECK5K_COUNT_HIT_T2: U_SERDES.44 (HIT_T2), U_TILE2.30 (count_hit_64b)
DECK5K_COUNT_HIT_T3: U_SERDES.56 (HIT_T3), U_TILE3.30 (count_hit_64b)
DECK5K_DONE_STICKY_T0: U_SERDES.133 (DONE_T0), U_TILE0.28 (done_sticky)
DECK5K_DONE_STICKY_T1: U_SERDES.141 (DONE_T1), U_TILE1.28 (done_sticky)
DECK5K_DONE_STICKY_T2: U_SERDES.50 (DONE_T2), U_TILE2.28 (done_sticky)
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
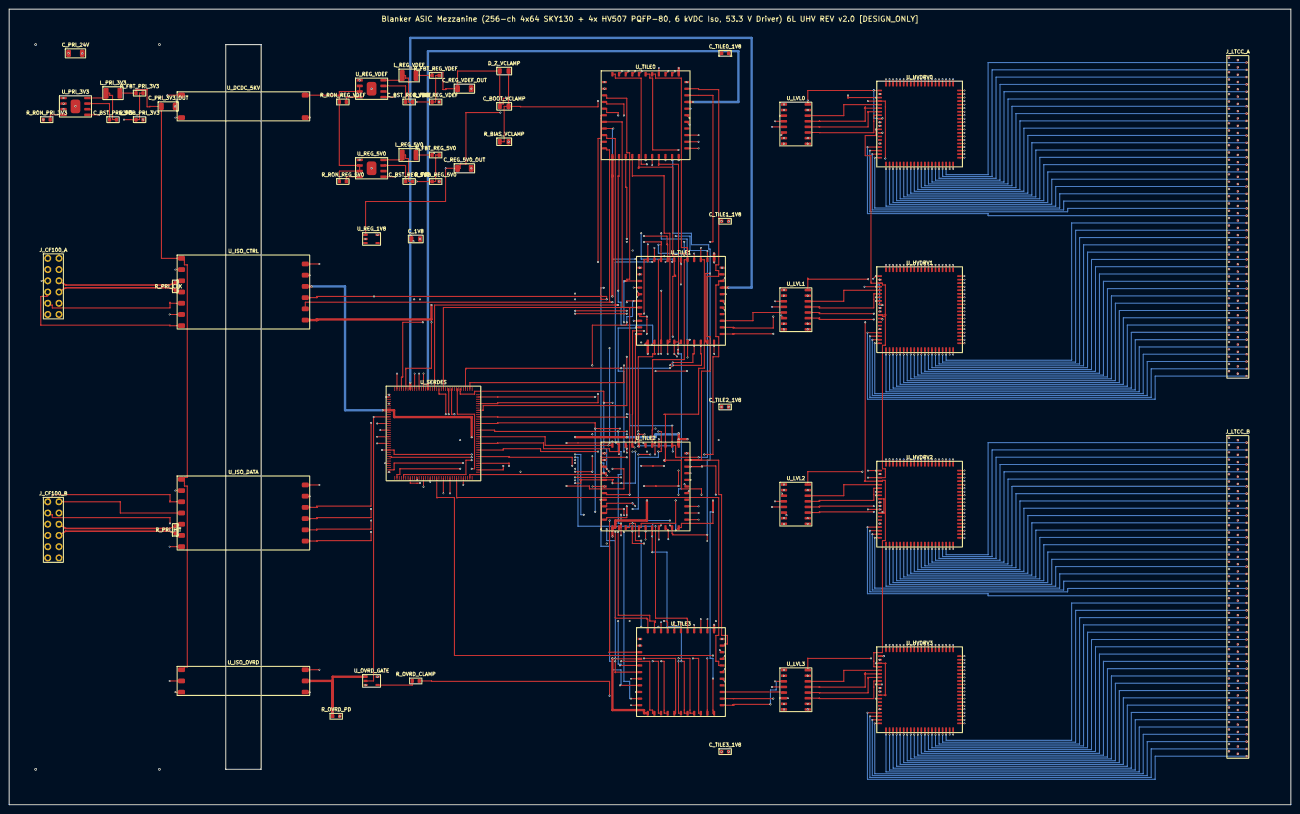
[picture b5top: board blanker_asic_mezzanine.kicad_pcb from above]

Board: 6 copper layers, 290.0 x 180.0 mm, 57 parts (0 on the bottom side), 372 nets.
